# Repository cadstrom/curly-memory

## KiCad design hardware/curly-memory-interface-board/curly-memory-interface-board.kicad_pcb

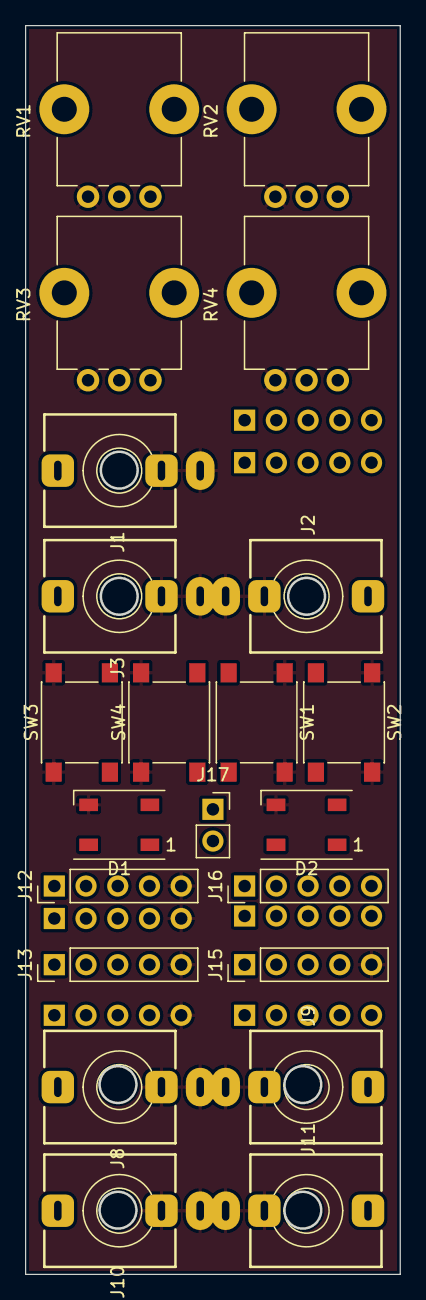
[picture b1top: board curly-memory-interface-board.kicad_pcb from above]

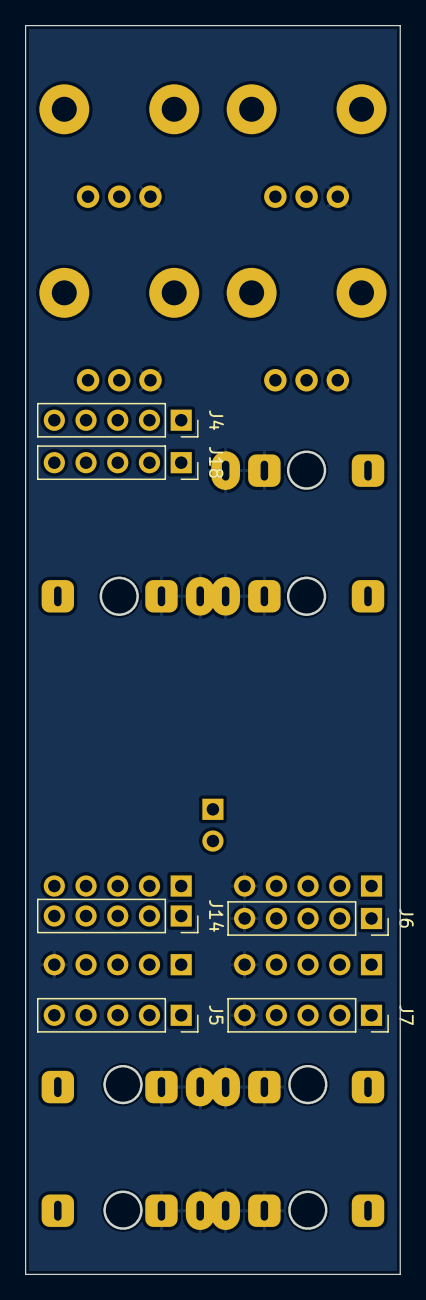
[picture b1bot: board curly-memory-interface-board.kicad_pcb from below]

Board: 2 copper layers, 30.0 x 100.0 mm, 28 parts (6 on the bottom side), 30 nets, no tracks yet.

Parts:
D1, D2: WS2812B; LED_WS2812B_PLCC4_5.0x5.0mm_P3.2mm
J1, J2, J3, J8, J9, J10, J11: AudioJack2; Jack_3.5mm_QingPu_WQP-PJ398SM_Vertical
J4, J5, J6, J7, J14, J18: Conn_01x05; PinSocket_1x05_P2.54mm_Vertical
J12, J13, J15, J16: Conn_01x05; PinHeader_1x05_P2.54mm_Vertical
J17: Conn_01x02; PinSocket_1x02_P2.54mm_Vertical
RV1, RV2, RV3, RV4: PTV09A-4225F-B203; Potentiometer_Bourns_PTV09A-1_Single_Vertical
SW1, SW2, SW3, SW4: FSM; SW_Push_1P1T_NO_6x6mm_H9.5mm

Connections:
+3V3: J14.4, J16.4
+5V: D1.1 (VDD), D2.1 (VDD), J14.5, J16.5, RV1.1, RV2.1, RV3.1, RV4.1
/BOOT: J6.1, J12.1, SW4.1, SW4.2
/DryWet: J5.1, J11.T
/IN_0: J1.T, J4.1
/IN_1: J2.T, J4.2
/IN_2: J3.T, J4.3, J15.3
/IN_3: J4.4, J15.1
/IO17: J14.1, J16.1
/IO21: J14.2, J16.2
/IO22: J14.3, J16.3
/LEDS: D1.4 (DIN), J7.4, J13.4
/OUT_0: J5.5, J8.T
/OUT_1: J5.4, J9.T
/OUT_2: J5.3, J10.T, J15.4
/OUT_3: J5.2, J15.2
/PROG_RX: J6.4, J12.4
/PROG_TX: J6.3, J12.3
/RES0_A1: J7.1, J13.1
/RES0_B1: J7.3, J13.3
/RES0_W1: J7.2, J13.2
/RES_0: J4.5, RV1.2
/RES_1: J18.1, RV2.2
/RES_2: J18.2, RV3.2
/RES_3: J18.3, RV4.2
/RST: J6.2, J12.2, SW3.1, SW3.2
/SW_0: J18.4, SW1.1, SW1.2
/SW_1: J18.5, SW2.1, SW2.2
GND: D1.3 (VSS), D2.3 (VSS), J1.S, J1.TN, J2.S, J2.TN, J3.S, J3.TN, J6.5, J7.5, J8.S, J8.TN, J9.S, J9.TN, J10.S, J10.TN, J11.S, J11.TN, J12.5, J13.5, J15.5, RV1.3, RV2.3, RV3.3, RV4.3, SW1.3 (K), SW1.4 (A), SW2.3 (K), SW2.4 (A), SW3.3 (K), SW3.4 (A), SW4.3 (K), SW4.4 (A)
unnamed: D1.2 (DOUT), D2.4 (DIN)

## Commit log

2022-01-15 Setup Cadstrom CI
2022-01-25 Fill copper zones
2022-05-18 Update yml to support kicad_sch files
